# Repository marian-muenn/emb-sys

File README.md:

# Projektdokumentation

## Projektstruktur

- `./platformio/`
  - Beinhaltet die Microcontrolleranwendung
- `./kicad/`
  - Beinhaltet das Platinenlayout
- `./docker-compose/`
  - Beinhaltet die docker-compose Datei für Datenbank, haproxy, mqtt-Broker und Grafana
- `./rust-backend/`
  - Beinhaltet das Backend um die Daten zu speichern

## Dockerumgebung

### Installation der benötigten Pakete

- docker-compose lässt sich über die Paketverwaltung der Linux Distribution installieren

### Hinterlegen der Zertifikate

- in `./docker-compose/ha/ssl/certs/` sind die Zertifikate für MQTT sowie Grafana- und EMQX-Webfrontend zu hinterlegen
- Die genauen Pfade sind der Datei `./docker-compose/ha/conf/haproxy.conf/` zu entnehmen.

### Anpassen der docker-compose Datei

- In der Datei `./docker-compose/docker-compose.yaml` sind die Benutzernamen und Passwörter für 
  Datenbank, mqtt und Grafana anzupassen

### Starten der Softwareumgebung

- Als Root-user kann die Softwareumgebung mit `docker-compose up -d` gestartet werden
- Docker downloadet dann alle Container automatisch und startet diese

## Rust Backend

### Installation von cargo

- Cargo ist das build tool von Rust
- Cargo kann über das Paketmanagement der Distribution  oder über [rustup](https://rustup.rs/) installiert werden

### Konfiguration der Datenbankanbindung

- In der Datei `rust-backend/Rocket.toml` sind Benutzername und Passwort für die Datenbankanbindung anzupassen.

### Kompilieren und Ausführen des Programmes

- Mit dem Befehl `cargo build` wird der Quellcode übersetzt und Abhängigkeiten werden automatisch aufgelöst
- Mit `cargo run` wird das Backend gestartet
- Achtung: Die Datenbank muss vorher laufen.

## Microcontrolleranwendung

### Installation von PlatformIO

- PlatformIO kann über den Paketmanger oder nach [der offiziellen Anleitung](https://docs.platformio.org/en/latest/core/installation/methods/index.html) installiert werden.
- Zum Übersetzen wird außerdem das Programm `make` benötigt.

### Kompilieren und Übertragen des Programmes

- Mit `make` wird das Programm kompiliert
- Mit `make flash` wird das Programm auf den Microcontroller übertragen

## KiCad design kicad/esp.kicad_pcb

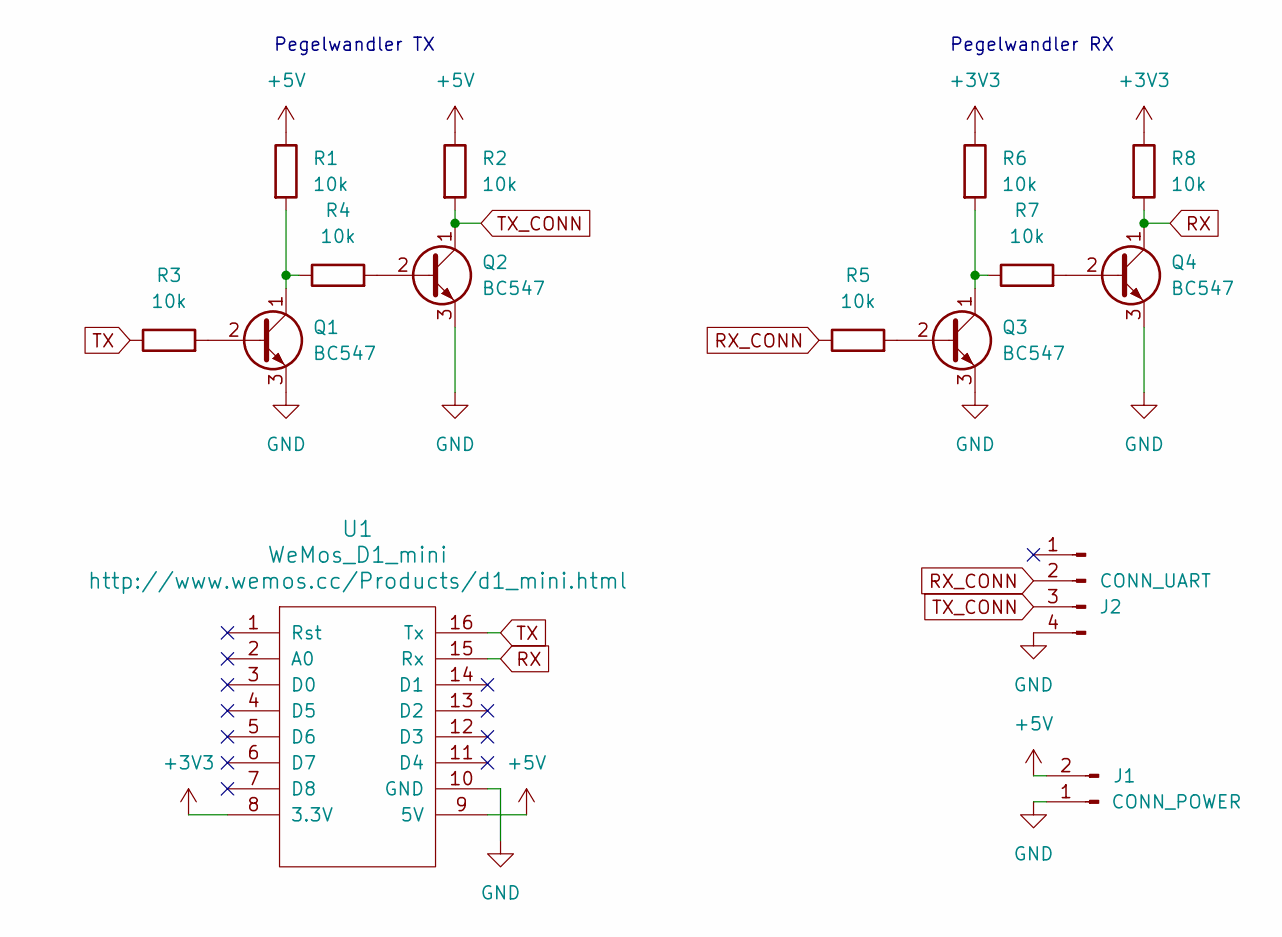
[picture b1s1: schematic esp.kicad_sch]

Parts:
J1: CONN_POWER; TerminalBlock_Phoenix_MKDS-3-2-5.08_1x02_P5.08mm_Horizontal
J2: CONN_UART; TerminalBlock_Phoenix_MKDS-3-4-5.08_1x04_P5.08mm_Horizontal
Q1, Q2, Q3, Q4: BC547; TO-92L_Inline_Wide
R1, R2, R3, R4, R5, R6, R7, R8: 10k; R_Axial_DIN0204_L3.6mm_D1.6mm_P5.08mm_Horizontal
U1: WeMos_D1_mini; wemos-d1-mini-with-pin-header-and-connector

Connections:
+3V3: R6.1, R8.1, U1.8 (3.3V)
+5V: J1.2, R1.1, R2.1, U1.9 (5V)
GND: J1.1, J2.4, Q1.3 (E), Q2.3 (E), Q3.3 (E), Q4.3 (E), U1.10 (GND)
unnamed: Q1.2 (B), R3.2
unnamed: Q1.1 (C), R1.2, R4.1
unnamed: Q2.2 (B), R4.2
unnamed: Q3.2 (B), R5.2
unnamed: Q3.1 (C), R6.2, R7.1
unnamed: Q4.2 (B), R7.2
RX: Q4.1 (C), R8.2, U1.15 (Rx)
RX_CONN: J2.2, R5.1
TX: R3.1, U1.16 (Tx)
TX_CONN: J2.3, Q2.1 (C), R2.2

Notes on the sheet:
Pegelwandler TX
Pegelwandler RX

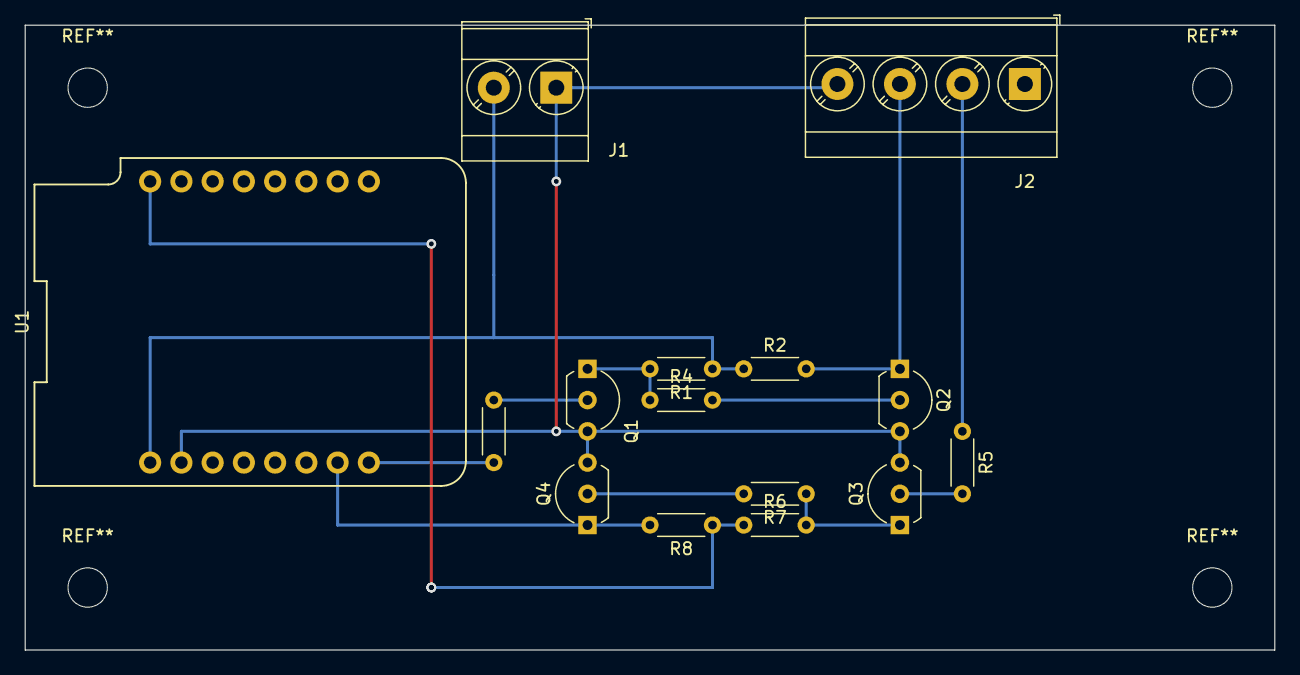
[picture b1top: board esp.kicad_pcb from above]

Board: 2 copper layers, 101.6 x 50.8 mm, 15 parts (0 on the bottom side), 13 nets.
